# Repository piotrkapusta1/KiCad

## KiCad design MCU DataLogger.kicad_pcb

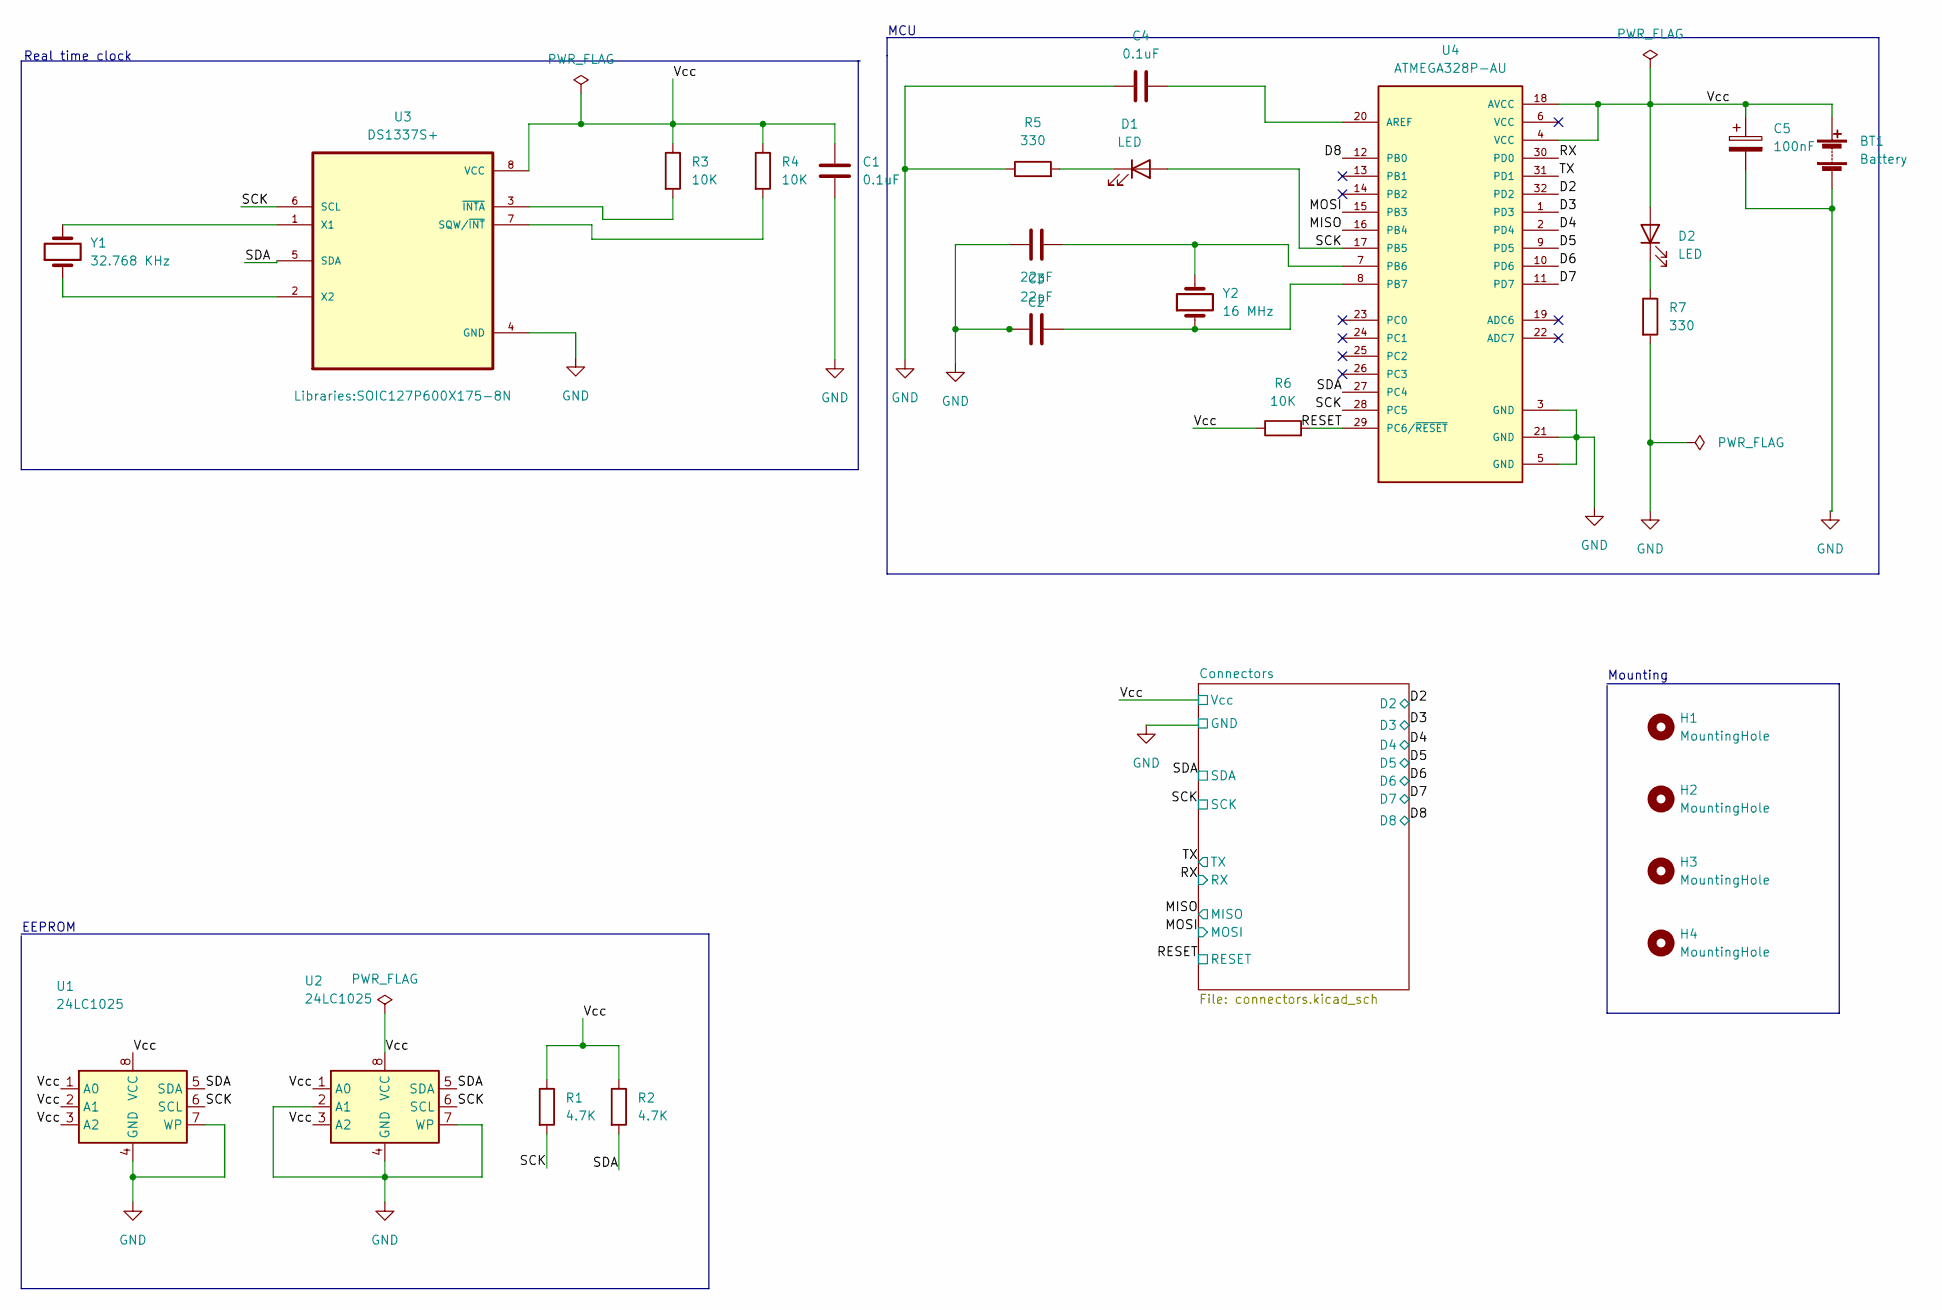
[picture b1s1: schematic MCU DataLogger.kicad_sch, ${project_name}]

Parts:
BT1: Battery; PinHeader_1x02_P2.54mm_Vertical
C1, C4: 0.1uF; C_0805_2012Metric
C2, C3: 22pF; C_0805_2012Metric
C5: 100nF; C_0805_2012Metric
D1, D2: LED; LED_0805_2012Metric
H1, H2, H3, H4: MountingHole; MountingHole_2.1mm
R1, R2: 4.7K; R_0805_2012Metric
R3, R4, R6: 10K; R_0805_2012Metric
R5, R7: 330; R_0805_2012Metric
U1, U2: 24LC1025; SOIC-8_5.23x5.23mm_P1.27mm
U3: DS1337S+; SOIC127P600X175-8N
U4: ATMEGA328P-AU; QFP80P900X900X120-32N
Y1: 32.768 KHz; Crystal_SMD_5032-2Pin_5.0x3.2mm_HandSoldering
Y2: 16 MHz; Crystal_SMD_5032-2Pin_5.0x3.2mm_HandSoldering

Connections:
/D2: U4.32 (PD2); also elsewhere on the board
/D3: U4.1 (PD3); also elsewhere on the board
/D4: U4.2 (PD4); also elsewhere on the board
/D5: U4.9 (PD5); also elsewhere on the board
/D6: U4.10 (PD6); also elsewhere on the board
/D7: U4.11 (PD7); also elsewhere on the board
/D8: U4.12 (PB0); also elsewhere on the board
/MISO: U4.16 (PB4); also elsewhere on the board
/MOSI: U4.15 (PB3); also elsewhere on the board
/RESET: R6.2, U4.29 (PC6/~RESET); also elsewhere on the board
/RX: U4.30 (PD0); also elsewhere on the board
/SCK: D1.2 (A), R1.2, U1.6 (SCL), U2.6 (SCL), U3.6 (SCL), U4.17 (PB5), U4.28 (PC5); also elsewhere on the board
/SDA: R2.2, U1.5 (SDA), U2.5 (SDA), U3.5 (SDA), U4.27 (PC4); also elsewhere on the board
/TX: U4.31 (PD1); also elsewhere on the board
/Vcc: BT1.1 (+), C1.1, C5.1, D2.2 (A), R1.1, R2.1, R3.1, R4.1, R6.1, U1.1 (A0), U1.2 (A1), U1.3 (A2), U1.8 (VCC), U2.1 (A0), U2.3 (A2), U2.8 (VCC), U3.8 (VCC), U4.4 (VCC), U4.18 (AVCC); also elsewhere on the board
GND: BT1.2 (-), C1.2, C2.1, C3.1, C4.1, C5.2, R5.1, R7.2, U1.4 (GND), U1.7 (WP), U2.2 (A1), U2.4 (GND), U2.7 (WP), U3.4 (GND), U4.3 (GND), U4.5 (GND), U4.21 (GND); also elsewhere on the board
unnamed: C3.2, U4.8 (PB7), Y2.1
unnamed: D1.1 (K), R5.2
unnamed: D2.1 (K), R7.1
unnamed: R3.2, U3.3 (~INTA)
unnamed: R4.2, U3.7 (SQW/~INT)
unnamed: U3.1 (X1), Y1.2
unnamed: U3.2 (X2), Y1.1
unnamed: C2.2, U4.7 (PB6), Y2.2
unnamed: C4.2, U4.20 (AREF)

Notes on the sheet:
Mounting
EEPROM
MCU
Real time clock

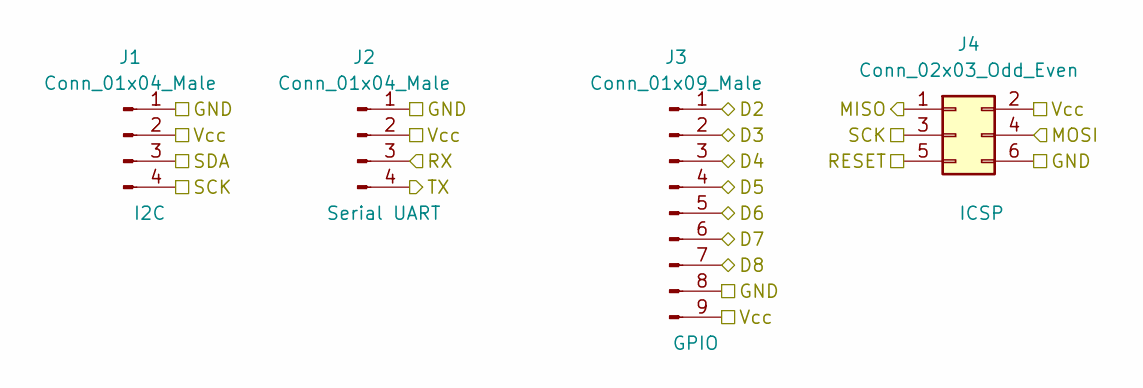
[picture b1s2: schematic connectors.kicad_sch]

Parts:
J1, J2: Conn_01x04_Male; PinHeader_1x04_P2.54mm_Vertical
J3: Conn_01x09_Male; PinHeader_1x09_P2.54mm_Vertical
J4: Conn_02x03_Odd_Even; PinHeader_2x03_P2.54mm_Vertical

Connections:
/D2: J3.1; also elsewhere on the board
/D3: J3.2; also elsewhere on the board
/D4: J3.3; also elsewhere on the board
/D5: J3.4; also elsewhere on the board
/D6: J3.5; also elsewhere on the board
/D7: J3.6; also elsewhere on the board
/D8: J3.7; also elsewhere on the board
/MISO: J4.1; also elsewhere on the board
/MOSI: J4.4; also elsewhere on the board
/RESET: J4.5; also elsewhere on the board
/RX: J2.3; also elsewhere on the board
/SCK: J1.4, J4.3; also elsewhere on the board
/SDA: J1.3; also elsewhere on the board
/TX: J2.4; also elsewhere on the board
/Vcc: J1.2, J2.2, J3.9, J4.2; also elsewhere on the board
GND: J1.1, J2.1, J3.8, J4.6; also elsewhere on the board

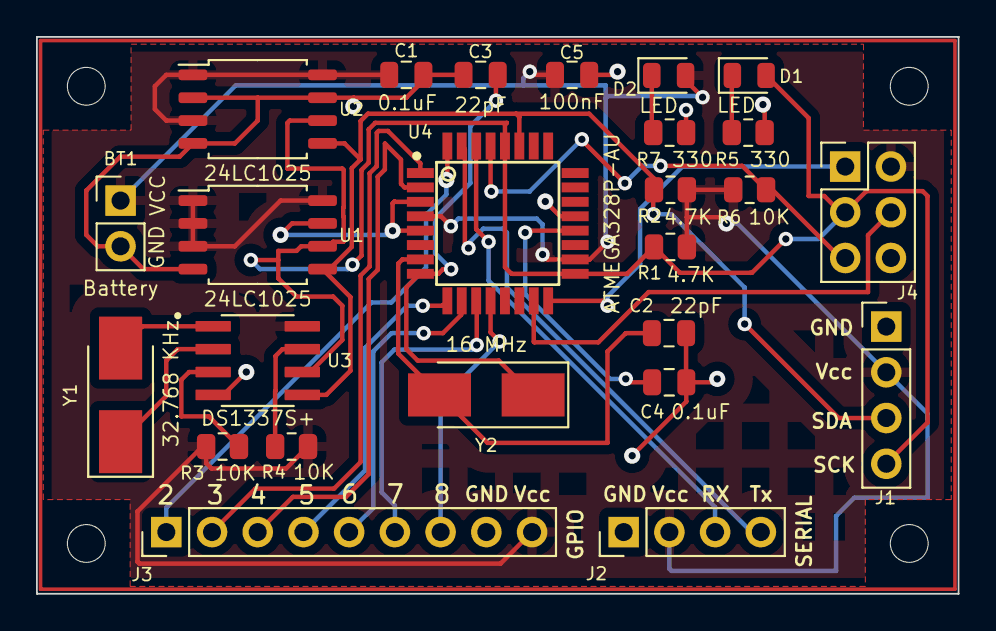
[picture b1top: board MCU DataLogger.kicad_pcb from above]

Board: 2 copper layers, 51.2 x 30.9 mm, 30 parts (1 on the bottom side), 25 nets.

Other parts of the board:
REF1: KiCad-Logo2_5mm_SilkScreen

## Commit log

2022-11-16 Fisrt commit
2022-11-16 Setup
2022-11-16 Have added required symbols
2022-11-17 Changes and add component values
2022-11-17 Completed symbol-footprint associations.
2022-11-17 Completed wiring of main sheet.
2022-11-18 Completed wiring
2022-11-18 Allocated GND and Vcc nets to the Power net class.
2022-11-18 Completed comments.
2022-11-18 Setup Pcbnew.
2022-11-18 Completed footprints.
2022-11-21 First routes.
2022-11-23 Routing sans GND Vcc complete.
2022-11-23 Add Cu surface 1/2
2022-11-24 Completed routing
2022-11-24 Add silkscreen
2022-11-24 Update silkscreen
2022-11-25 Fixed outstanding issues.
2022-11-25 End of the project
2022-11-28 Added gerber directories
2022-11-28 Added gerber directories to git
